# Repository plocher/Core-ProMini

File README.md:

# Core-ProMini
## License: CERN Open Hardware Licence v1.2

IO4-based Arduino ProMini baseboard

This design evolved from my Core-ArduinoShield sequence when it became obvious that
the eBay ProMini clones were much cheaper than full sized Arduinos and their clones.

Until the [Core Wemos D1 Mini](/Core-Wemos.html) and [Core-ESP32](/Core-ESP32.html) boards,
this was my go-to building block for field units and other layout automation tasks.

V2.0 has an onboard Loconet interface, V3.0 removes it

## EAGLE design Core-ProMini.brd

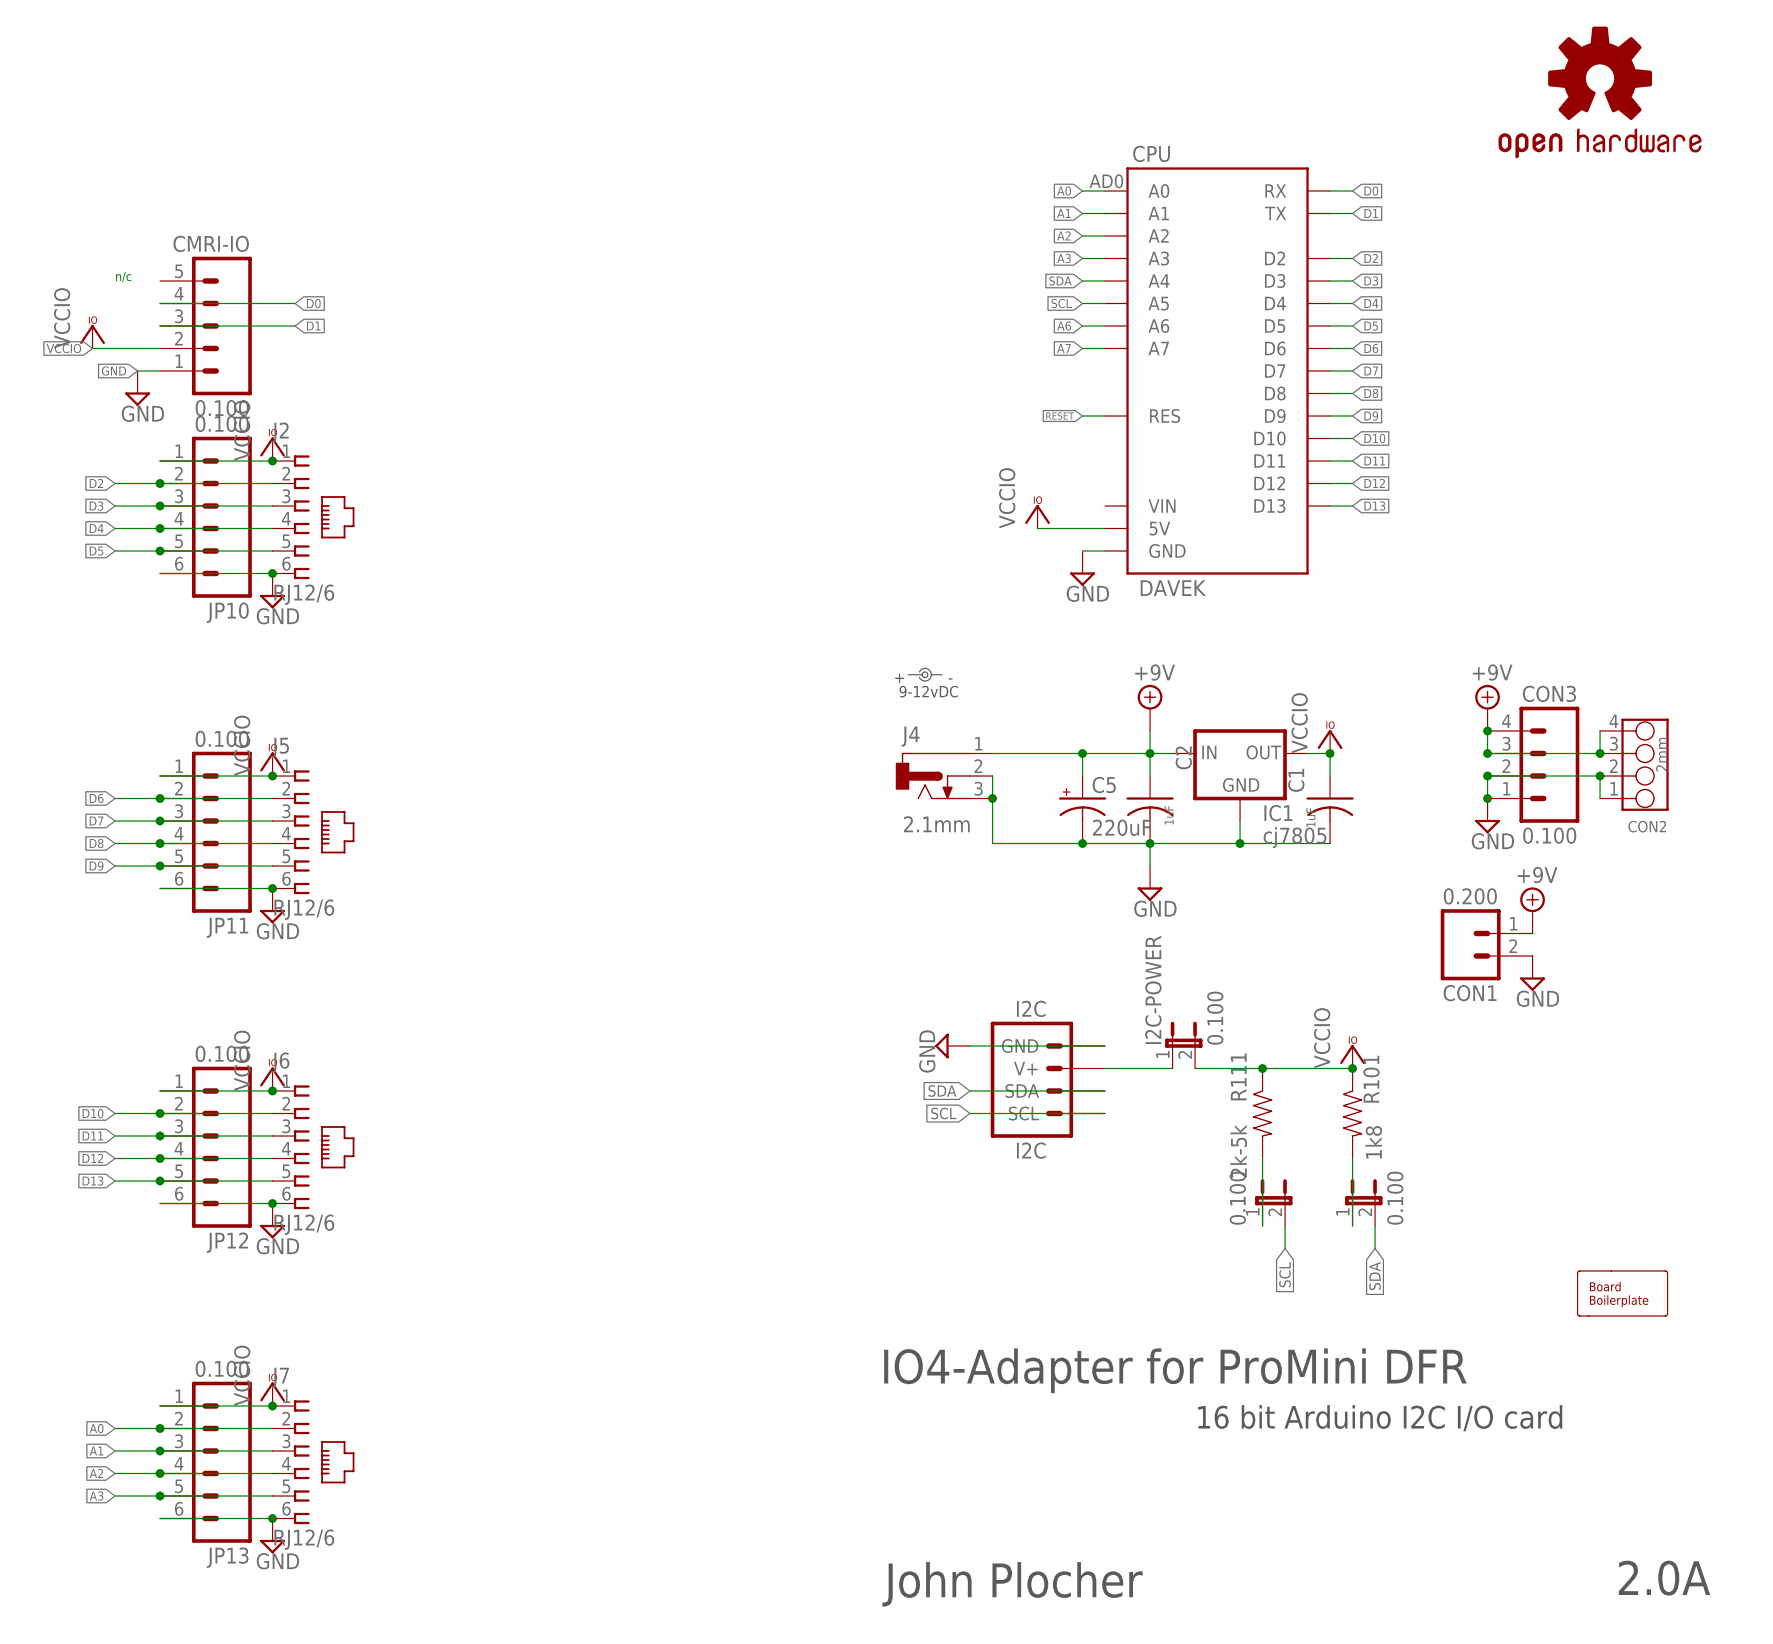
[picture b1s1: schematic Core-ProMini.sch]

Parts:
BOARD: BOARD; BOARD-DINRAIL-3.17INX10CM
C1, C2: 1uF; 0603-CAP
C5: 220uF; 0810-CAP
CMRI-IO: 0.100; 1X05-CMRI-IO
CON1: 0.200; MSTB2
CON2: 2mm; 4P-2.0
CON3: 0.100; 1X04_LOCK
CPU: DAVEK; ARDUINO_PRO_MINI_DAVEK
I2C: I2C; I2C-L
I2C-POWER: 0.100; 1X02_LOCK
IC1: cj7805; TO-252
J2, J5, J6, J7: RJ12/6; RJ25-PANEL
J4: 2.1mm; DCJ0202
JP10, JP11, JP12, JP13: 0.100; 1X06_LOCK
OSH: OSHW; OSHW-LOGO-L
PWR: 9-12vDC; PWR_LABEL
R101: 1k8; 0603-RES
R111: 2k-5k; 0603-RES
SCL: 0.100; 1X02_LOCK
SDA: 0.100; 1X02_LOCK

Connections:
+9V: C2.1, C5.+, CON1.1 (A), CON2.3, CON2.4, CON3.3, CON3.4, IC1.1 (IN), J4.1
A0: CPU.AD0 (A0), J7.2, JP13.2
A1: CPU.AD1 (A1), J7.3, JP13.3
A2: CPU.AD2 (A2), J7.4, JP13.4
A3: CPU.AD3 (A3), J7.5, JP13.5
A6: CPU.AD6 (A6)
A7: CPU.AD7 (A7)
D0: CMRI-IO.4, CPU.RX
D1: CMRI-IO.3, CPU.TX@1 (TX)
D2: CPU.D2, J2.2, JP10.2
D3: CPU.D3, J2.3, JP10.3
D4: CPU.D4, J2.4, JP10.4
D5: CPU.D5, J2.5, JP10.5
D6: CPU.D6, J5.2, JP11.2
D7: CPU.D7, J5.3, JP11.3
D8: CPU.D8, J5.4, JP11.4
D9: CPU.D9, J5.5, JP11.5
D10: CPU.D10, J6.2, JP12.2
D11: CPU.D11, J6.3, JP12.3
D12: CPU.D12, J6.4, JP12.4
D13: CPU.D13, J6.5, JP12.5
GND: C1.2, C2.2, C5.-, CMRI-IO.1, CON1.2 (B), CON2.1, CON2.2, CON3.1, CON3.2, CPU.GND@1 (GND), CPU.GND@2 (GND), CPU.GND@4 (GND), I2C.GND, I2C.GND@1 (GND), IC1.2 (GND), J2.6, J4.2, J4.3, J5.6, J6.6, J7.6, JP10.6, JP11.6, JP12.6, JP13.6
unnamed: R111.2, SCL.1
unnamed: R101.2, SDA.1
unnamed: I2C.V+, I2C.V+@1 (V+), I2C-POWER.1
RESET: CPU.RES, CPU.RES@1 (RES)
SCL: CPU.AD5 (A5), I2C.SCL, I2C.SCL@1 (SCL), SCL.2
SDA: CPU.AD4 (A4), I2C.SDA, I2C.SDA@1 (SDA), SDA.2
VCCIO: C1.1, CMRI-IO.2, CPU.5V, I2C-POWER.2, IC1.3 (OUT), J2.1, J5.1, J6.1, J7.1, JP10.1, JP11.1, JP12.1, JP13.1, R101.1, R111.1

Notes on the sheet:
IO4-Adapter for ProMini DFR
16 bit Arduino I2C I/O card
John Plocher
2.0A
n/c

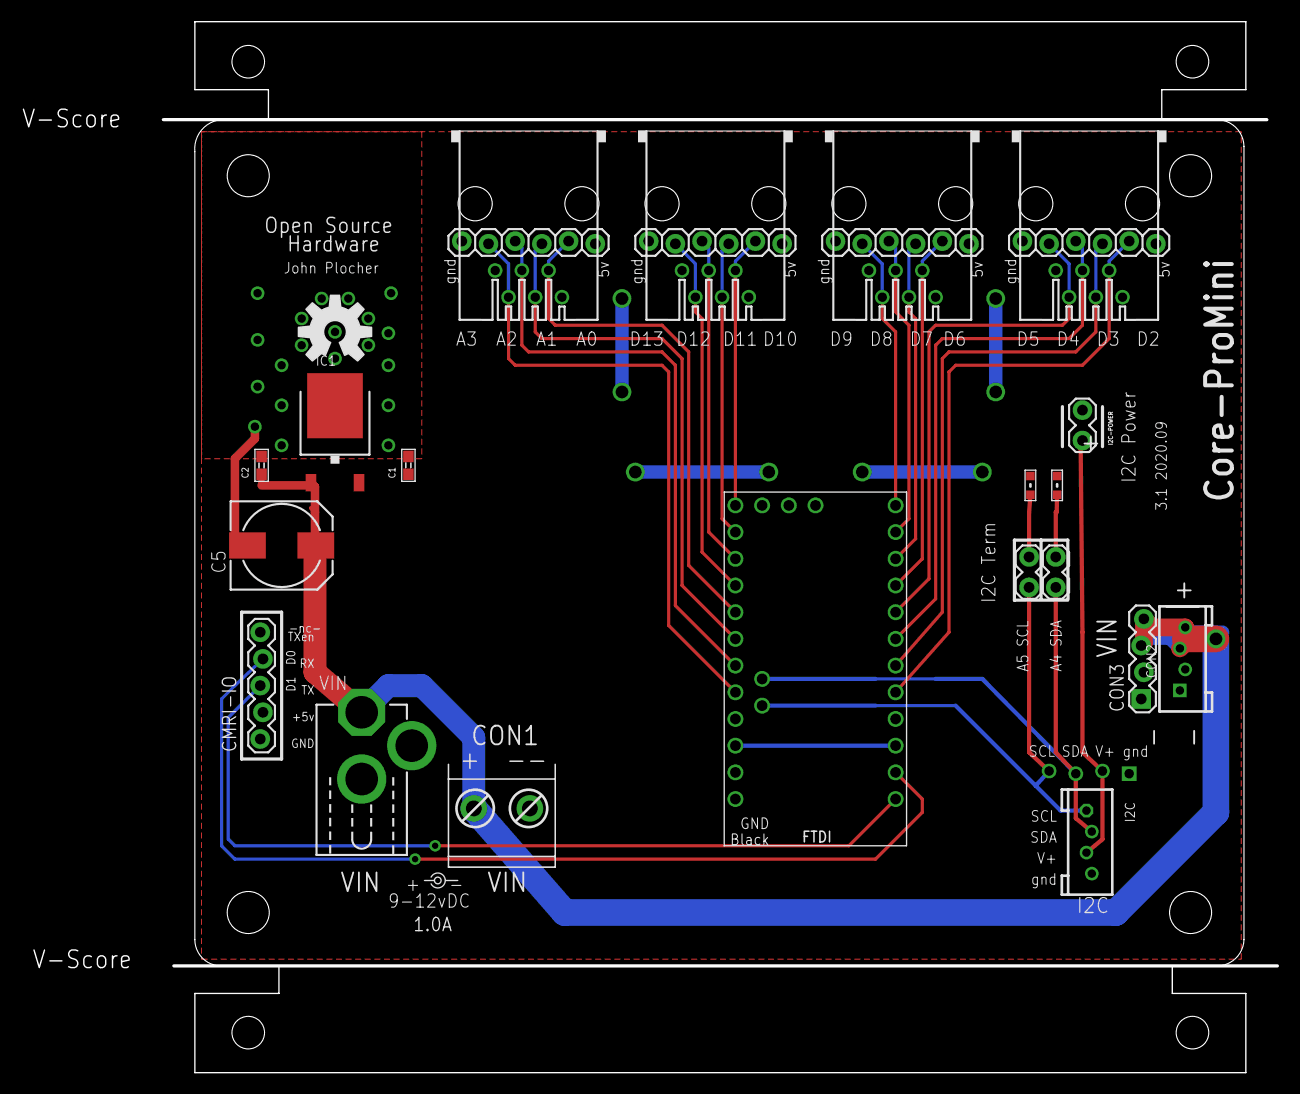
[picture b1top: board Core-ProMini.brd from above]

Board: 2 copper layers, 119.4 x 99.8 mm, 27 parts (0 on the bottom side), 27 nets.

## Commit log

2019-11-24 fixed links
2019-11-28 removed loconet interface
2019-11-28 also removed LEDs
2019-12-03 Create LICENSE
2019-12-03 Update LICENSE
2019-12-03 done experimenting
2019-12-09 added graphic
2020-05-04 updated tags
2020-09-19 updated part values and silkscreen, added cmri-io
2020-09-19 updated part names
2020-10-06 normalized values
